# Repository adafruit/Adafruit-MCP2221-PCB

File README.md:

## Adafruit MCP2221 PCB

<a href="http://www.adafruit.com/products/4471"><br/>
Click here to purchase one from the Adafruit shop</a>

PCB files for the Adafruit MCP2221. 

Format is EagleCAD schematic and board layout
* https://www.adafruit.com/product/4471

### Description

The MCP2221 allows you to connect I2C sensors and breakouts to your PC running Windows, Linux, Mac OSX, or Linux. It also allows for general purpose digital inout and output (GPIO) for things like buttons and LEDs, analog to fdigital conversion (ADC), and digital to analog (DAC).

### License

Adafruit invests time and resources providing this open source design, please support Adafruit and open-source hardware by purchasing products from [Adafruit](https://www.adafruit.com)!

Designed by Limor Fried/Ladyada for Adafruit Industries.

Creative Commons Attribution/Share-Alike, all text above must be included in any redistribution. 
See license.txt for additional details.

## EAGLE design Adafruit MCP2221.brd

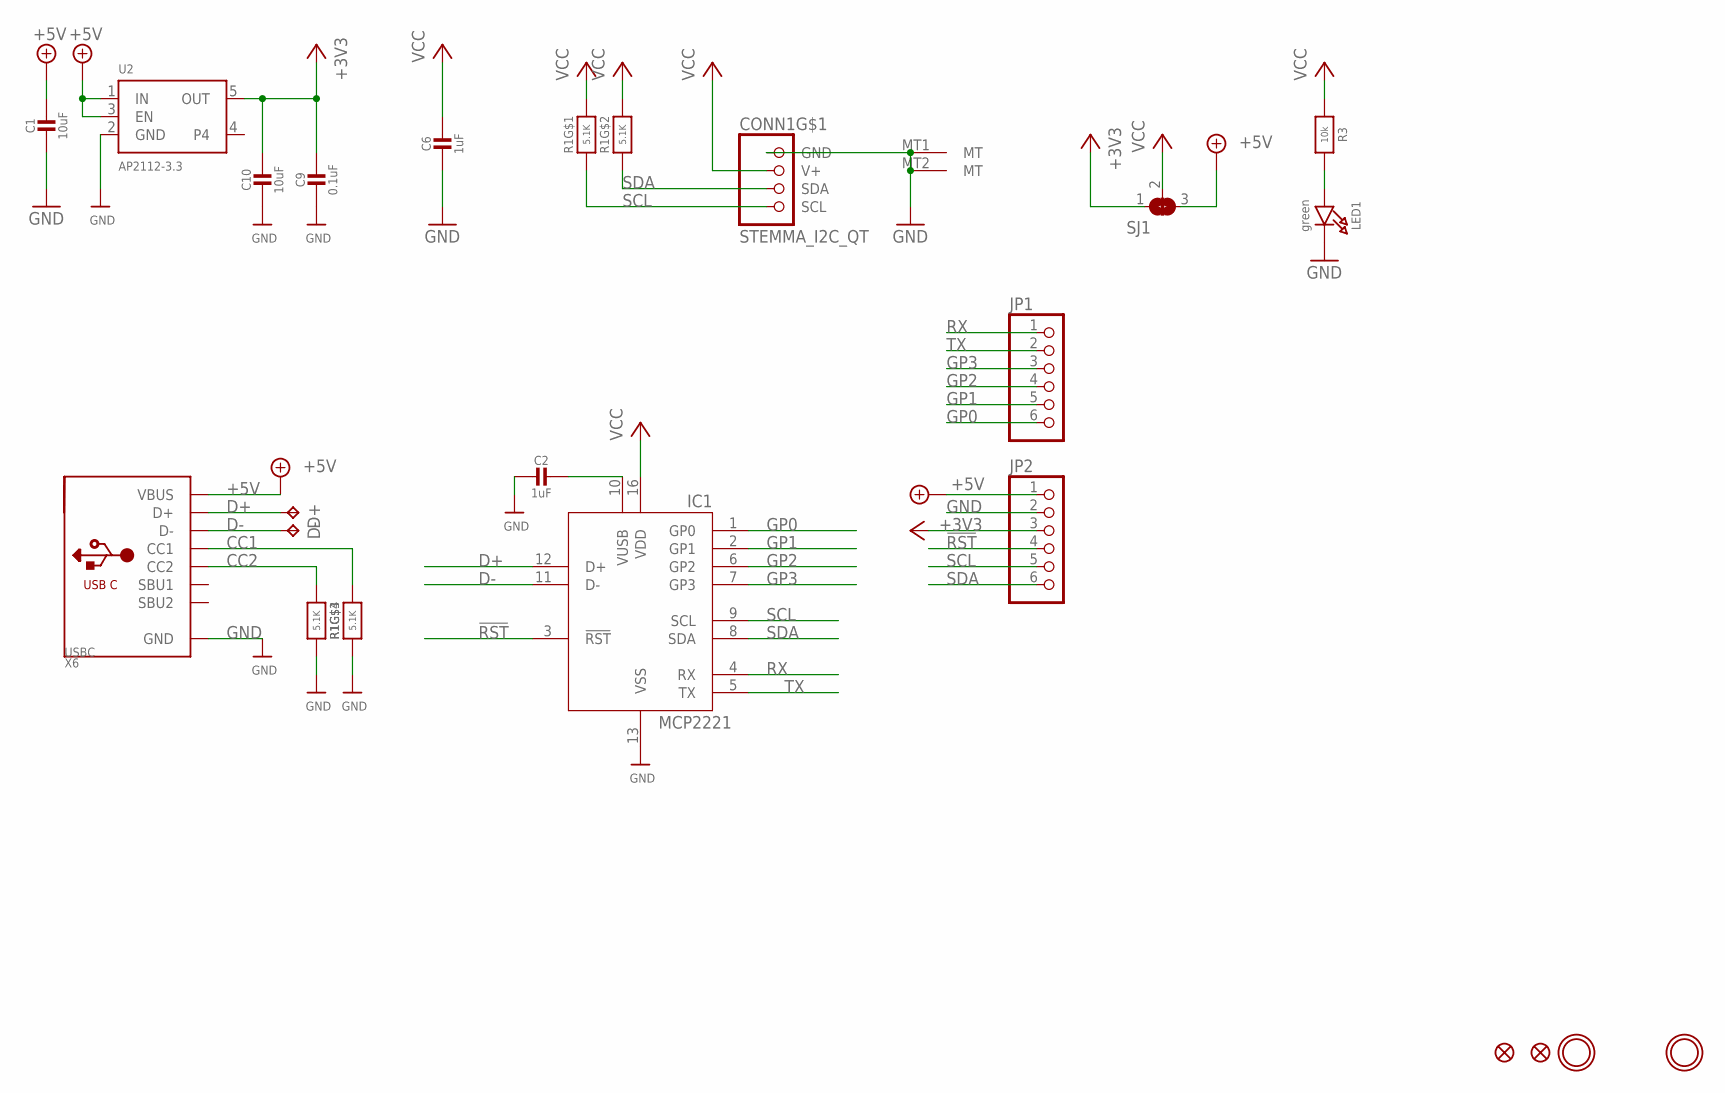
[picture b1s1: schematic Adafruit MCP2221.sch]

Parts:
C1, C10: 10uF; 0805-NO
C2, C6: 1uF; 0603-NO
C9: 0.1uF; 0603-NO
CONN1: STEMMA_I2C_QT; JST_SH4
D+: TPTP17R; TP17R
D-: TPTP17R; TP17R
FID1, FID2: FIDUCIAL_1MM
IC1: MCP2221_ML; QFN16_4MM
JP1, JP2: HEADER-1X670MIL; 1X06_ROUND_70
LED1: green; CHIPLED_0603_NOOUTLINE
R1: 5.1K; RESPACK_4X0603
R3: 10k; 0603-NO
SJ1: SOLDERJUMPER_2WAY; SOLDERJUMPER_2WAY_OPEN_NOPASTE
U2: AP2112-3.3; SOT23-5
U$6, U$7: MOUNTINGHOLE2.5; MOUNTINGHOLE_2.5_PLATED
X6: USBC; USB_C_CUSB31-CFM2AX-01-X

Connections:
!RST: IC1.3 (!RST), JP2.4
+3V3: C9.1, C10.1, JP2.3, SJ1.1, U2.5 (OUT)
+5V: C1.1, JP2.1, SJ1.3, U2.1 (IN), U2.3 (EN), X6.A4B9 (VBUS), X6.B4A9 (VBUS)
CC1: R1.6 (2), X6.A5 (CC1)
CC2: R1.4 (1), X6.B5 (CC2)
D+: D+.TP, IC1.12 (D+), X6.A6 (D+), X6.B6 (D+)
D-: D-.TP, IC1.11 (D-), X6.A7 (D-), X6.B7 (D-)
GND: C1.2, C2.2, C6.2, C9.2, C10.2, CONN1.1 (GND), CONN1.MT1 (MT), CONN1.MT2 (MT), IC1.13 (VSS), JP2.2, LED1.C, R1.3 (1), R1.5 (2), U2.2 (GND), X6.A1B12 (GND), X6.B1A12 (GND)
GP0: IC1.1 (GP0), JP1.6
GP1: IC1.2 (GP1), JP1.5
GP2: IC1.6 (GP2), JP1.4
GP3: IC1.7 (GP3), JP1.3
unnamed: C2.1, IC1.10 (VUSB)
unnamed: LED1.A, R3.2
RX: IC1.4 (RX), JP1.1
SCL: CONN1.4 (SCL), IC1.9 (SCL), JP2.5, R1.1
SDA: CONN1.3 (SDA), IC1.8 (SDA), JP2.6, R1.2 (1)
TX: IC1.5 (TX), JP1.2
VCC: C6.1, CONN1.2 (V+), IC1.16 (VDD), R1.7 (2), R1.8 (2), R3.1, SJ1.2

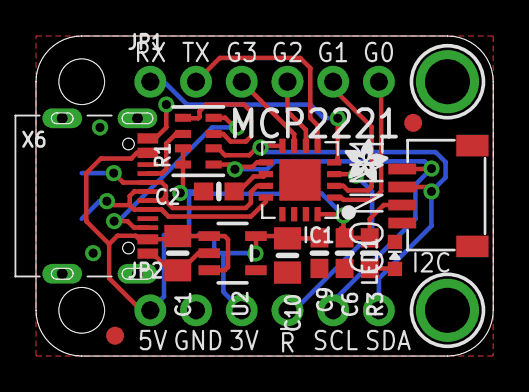
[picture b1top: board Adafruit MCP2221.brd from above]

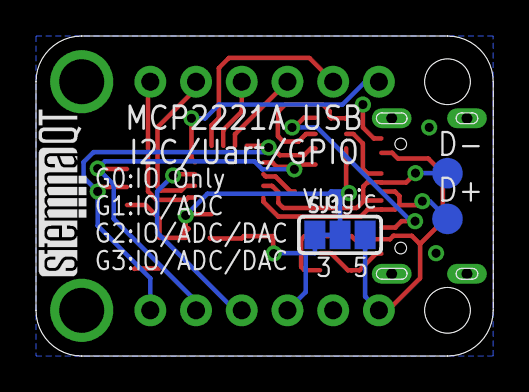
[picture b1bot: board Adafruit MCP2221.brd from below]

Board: 2 copper layers, 25.4 x 17.8 mm, 23 parts (4 on the bottom side), 19 nets.

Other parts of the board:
U$2: ADAFRUIT_2.5MM
U$3: STEMMAQT

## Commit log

2019-12-20 Adding PCB repo files.

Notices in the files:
parts and their libraries:
microbuilder: This work is placed in the public domain, and may be freely used for commercial and non-commercial work with the following conditions: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
